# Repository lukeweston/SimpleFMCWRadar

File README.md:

This relatively compact, cheap, simple FMCW radar operates in the spectrum around 5.8-6.0 GHz and is aimed at lowering the barrier to entry for experiments with radar and general education around RF and microwave electronics. It is capable of speed measurement,
rangefinding and SAR imaging (with appropriate moving antennas or a moving vehicle.) It is potentially applicable to experiments with autonomous aircraft (or spacecraft) altitude-finding, SAR imaging/mapping or navigation as an alternative to (or in addition to)
other sensing techniques such as GPS, ultrasonics, LIDAR or barometry, without some of the limitations applicable to those technologies.

This is still an early prototype, a rough quick work that is still very much in progress and evolving as bits are designed and built and redesigned.

Frequency-modulated RF is generated by the HMC431 VCO, at about 5.8-6.0 GHz, amplified by a HMC476 MMIC gain block, and split in half by the Wilkinson divider. Half the RF output from the divider is amplified again and sent to the transmit antenna connector.
The local oscillator, from the other side of the splitter, is amplified again and applied to the LO port of the HMC219 double-balanced mixer. The reflected RF from the receive antenna comes in to the HMC717 6 GHz LNA where it is amplified, and the amplified output is
fed into the mixer.

A couple of pi attenuators are used, after the VCO, before the mixer LO port and after the mixer's IF output, to "tune" optimal mixer LO level and overall performance. Although I haven't fixed certain values for these attenuators yet, space for them is left on
the board.

IF filtering, amplification and signal processing, along with generation of the 0-10V modulation signal for the VCO, are done on a separate board.

Source files - EDA/CAD information: These are CadSoft EAGLE files. See www.cadsoftusa.com/ for download and licensing information. The "free as in beer" "light" Eagle license is perfectly capable of opening and editing these files - the boards are only two-layer and
are relatively small. A PDF schematic is provided along with industry-standard fabrication-ready RS274X (Gerber) files.

License information: Open Hardware as per the CERN Open Hardware License; please see license.txt

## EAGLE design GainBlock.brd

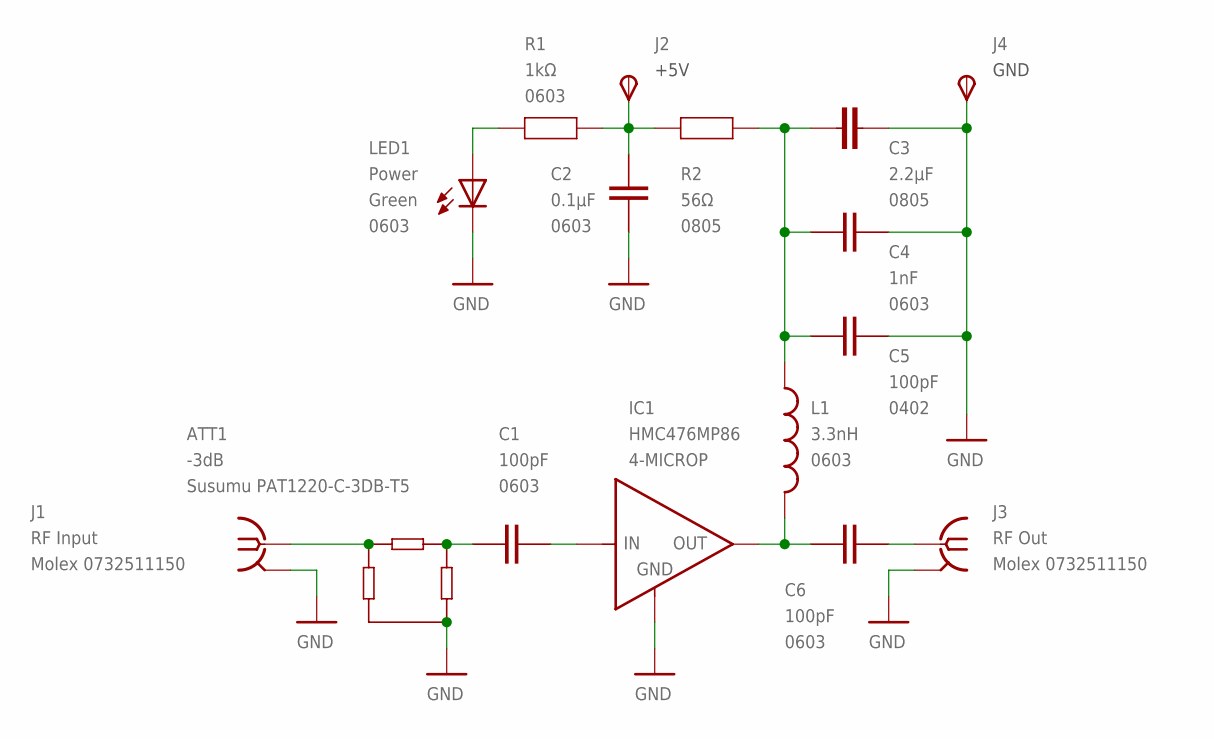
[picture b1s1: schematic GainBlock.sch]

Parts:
ATT1: -3dB; PAT1220
C1, C6: 100pF; 0603
C2: 0.1µF; 0603
C3: 2.2µF; 0805; VOLTAGE 10V
C4: 1nF; 0603
C5: 100pF; 0402
IC1: HMC476MP86; WW107
J1: RF Input; J502-ND-142-0701-881/886; MPN 142-0701-881
J2, J4: TPSPAD1-13; P1-13
J3: RF Out; J502-ND-142-0701-881/886; MPN 142-0701-881
L1: 3.3nH; 0603
LED1: Power; LED-0603
R1: 1kΩ; 0603
R2: 56Ω; 0805

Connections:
GND: ATT1.3, C2.2, C3.1, C4.2, C5.2, IC1.2 (GND), IC1.4 (GND), J1.G@1 (GND), J1.G@2 (GND), J1.G@3 (GND), J1.G@4 (GND), J3.G@1 (GND), J3.G@2 (GND), J3.G@3 (GND), J3.G@4 (GND), J4.TP, LED1.C
unnamed: ATT1.1, J1.1
unnamed: ATT1.2, C1.1
unnamed: LED1.A, R1.1
unnamed: C6.2, J3.1
unnamed: C1.2, IC1.1 (IN)
unnamed: C6.1, IC1.3 (OUT), L1.2
unnamed: C3.2, C4.1, C5.1, L1.1, R2.1
unnamed: C2.1, J2.TP, R1.2, R2.2

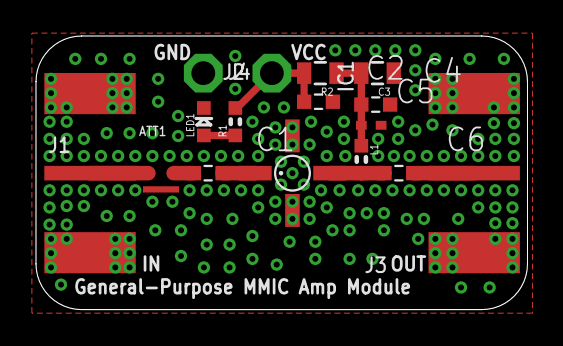
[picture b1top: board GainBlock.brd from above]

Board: 2 copper layers, 27.3 x 15.2 mm, 16 parts (0 on the bottom side), 9 nets.

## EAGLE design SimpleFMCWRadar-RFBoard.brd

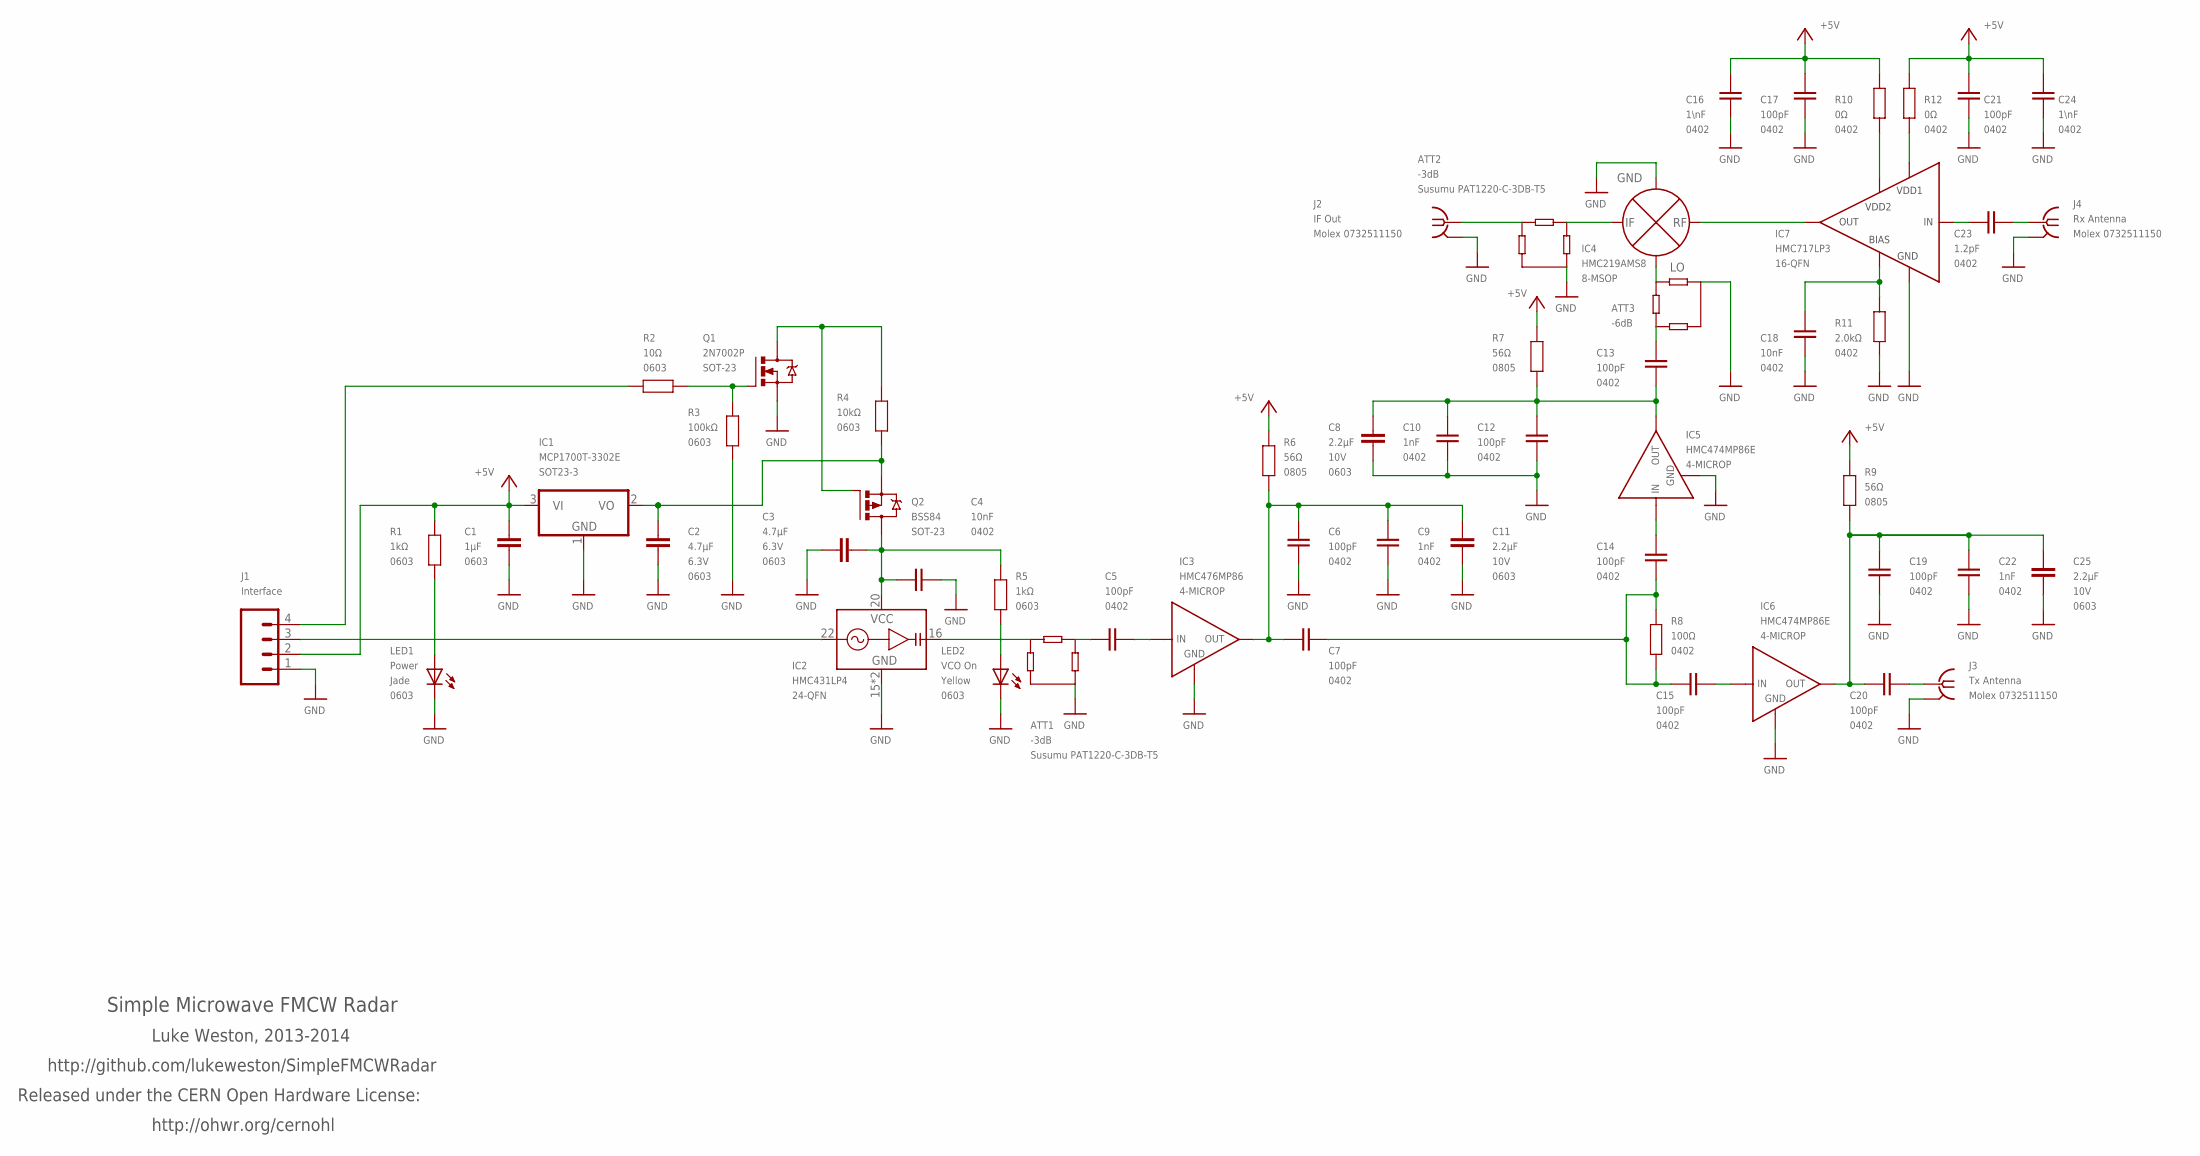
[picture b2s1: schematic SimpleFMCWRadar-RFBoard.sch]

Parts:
ATT1, ATT2: -3dB; PAT1220
ATT3: -6dB; PAT1220
C1: 1µF; 0603
C2, C3: 4.7µF; 0603; VOLTAGE 6.3V
C4, C18: 10nF; 0402
C5, C6, C7, C12, C13, C14, C15, C17, C19, C20, C21: 100pF; 0402
C8, C11, C25: 2.2µF; 0603; VOLTAGE 10V
C9, C10, C22: 1nF; 0402
C16, C24: 1\nF; 0402
C23: 1.2pF; 0402
IC1: MCP1700T-3302E; SOT23
IC2: HMC431LP4; QFN24
IC3: HMC476MP86; WW107
IC4: HMC219AMS8; 8-MSOP
IC5, IC6: HMC474MP86E; WW107
IC7: HMC717LP3; 16-QFN
J1: Interface; 1X04
J2: IF Out; J502-ND-142-0701-881/886; MPN 142-0701-881
J3: Tx Antenna; J502-ND-142-0701-881/886
J4: Rx Antenna; J502-ND-142-0701-881/886
LED1: Power; LED-0603
LED2: VCO On; LED-0603
Q1: 2N7002P; SOT23-3
Q2: BSS84; SOT23-3
R1, R5: 1kΩ; 0603
R2: 10Ω; 0603
R3: 100kΩ; 0603
R4: 10kΩ; 0603
R6, R7, R9: 56Ω; 0805
R8: 100Ω; 0402
R10, R12: 0Ω; 0402
R11: 2.0kΩ; 0402

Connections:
+5V: C1.2, C16.2, C17.2, C21.2, C24.2, IC1.3 (VI), J1.2, R1.2, R6.2, R7.1, R9.1, R10.2, R12.2
GND: ATT1.3, ATT2.3, ATT3.3, C1.1, C2.2, C3.2, C4.2, C6.1, C8.1, C9.1, C10.1, C11.1, C12.1, C16.1, C17.1, C18.1, C19.2, C21.1, C22.2, C24.1, C25.1, IC1.1 (GND), IC2.15 (GND), IC2.EXP (GND), IC3.2 (GND), IC3.4 (GND), IC4.1 (GND), IC4.3 (GND), IC4.6 (GND), IC4.8 (GND), IC5.2 (GND), IC5.4 (GND), IC6.2 (GND), IC6.4 (GND), IC7.P$1 (GND), IC7.P$3 (GND), IC7.P$4 (GND), IC7.P$5 (GND), IC7.P$6 (GND), IC7.P$7 (GND), IC7.P$9 (GND), IC7.P$10 (GND), IC7.P$12 (GND), IC7.P$14 (GND), IC7.P$16 (GND), IC7.PAD (GND), J1.1, J2.G@1 (GND), J2.G@2 (GND), J2.G@3 (GND), J2.G@4 (GND), J3.G@1 (GND), J3.G@2 (GND), J3.G@3 (GND), J3.G@4 (GND), J4.G@1 (GND), J4.G@2 (GND), J4.G@3 (GND), J4.G@4 (GND), LED1.C, LED2.C, Q1.2 (S), R3.1, R11.1
unnamed: C5.2, IC3.1 (IN)
unnamed: C6.2, C7.1, C9.2, C11.2, IC3.3 (OUT), R6.1
unnamed: ATT1.2, C5.1
unnamed: ATT1.1, IC2.16 (RFOUT)
unnamed: IC2.22 (VTUNE), J1.3
unnamed: C15.1, IC6.1 (IN)
unnamed: C7.2, C14.1, C15.2, R8.1, R8.2
unnamed: C20.1, J3.1
unnamed: ATT3.2, IC4.2 (LO)
unnamed: Q1.1 (G), R2.1, R3.2
unnamed: ATT2.2, IC4.5 (IF)
unnamed: C23.2, IC7.P$2 (IN)
unnamed: C23.1, J4.1
unnamed: IC4.7 (RF), IC7.P$11 (OUT)
unnamed: C18.2, IC7.P$8 (BIAS), R11.2
unnamed: IC7.P$13 (VDD2), R10.1
unnamed: IC7.P$15 (VDD1), R12.1
unnamed: LED1.A, R1.1
unnamed: ATT3.1, C13.2
unnamed: C3.1, C4.1, IC2.20 (VCC), Q2.3 (D), R5.2
unnamed: C2.1, IC1.2 (VO), Q2.2 (S), R4.1
unnamed: Q1.3 (D), Q2.1 (G), R4.2
unnamed: J1.4, R2.2
unnamed: C19.1, C20.2, C22.1, C25.2, IC6.3 (OUT), R9.2
unnamed: LED2.A, R5.1
unnamed: C8.2, C10.2, C12.2, C13.1, IC5.3 (OUT), R7.2
unnamed: C14.2, IC5.1 (IN)
unnamed: ATT2.1, J2.1

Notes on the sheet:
Simple Microwave FMCW Radar
Luke Weston, 2013-2014
http://github.com/lukeweston/SimpleFMCWRadar
Released under the CERN Open Hardware License:
http://ohwr.org/cernohl

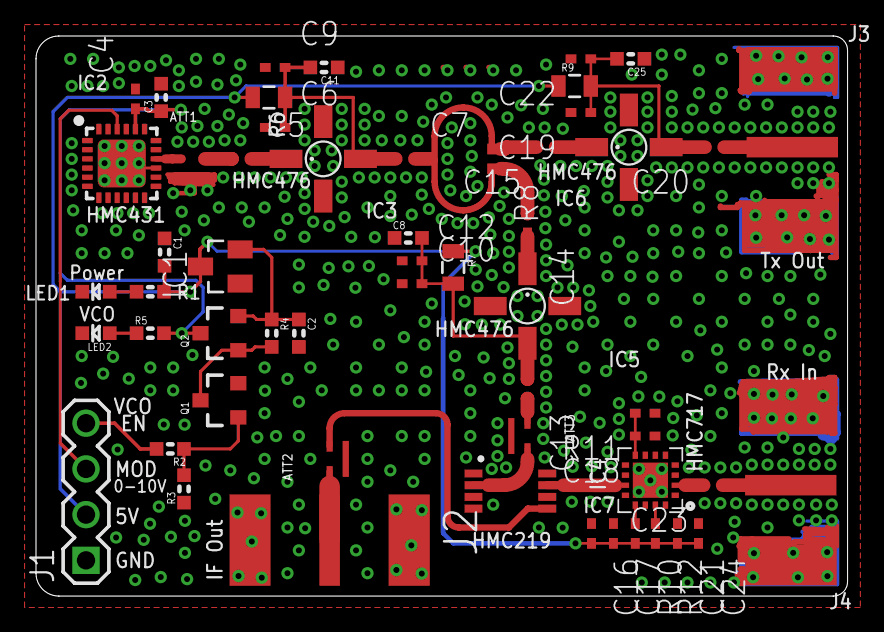
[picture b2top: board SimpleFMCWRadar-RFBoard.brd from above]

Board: 2 copper layers, 45.1 x 31.1 mm, 55 parts (0 on the bottom side), 30 nets.

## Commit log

2014-07-07 added readme and license
2014-07-07 added schematic
2014-07-07 added magical eagle CAM makefile
2014-07-07 added current RF board
2014-08-21 started collecting together some very basic software pieces in one place
2014-09-29 added gain block breakout module
